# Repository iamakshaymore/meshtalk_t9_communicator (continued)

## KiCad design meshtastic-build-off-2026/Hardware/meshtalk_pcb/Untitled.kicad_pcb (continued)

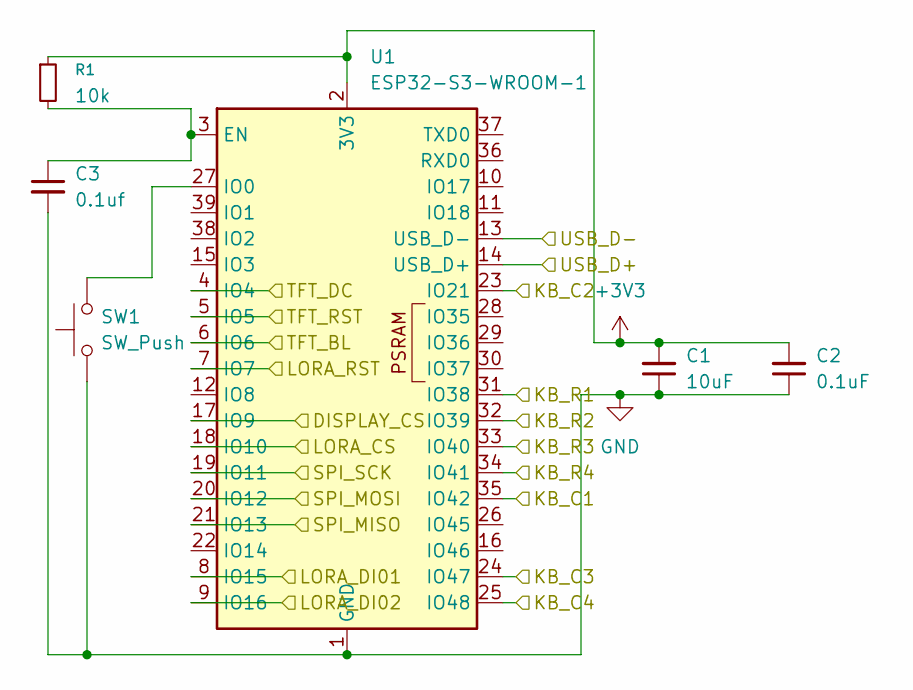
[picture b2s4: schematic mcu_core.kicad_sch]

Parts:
C1: 10uF; C_0805_2012Metric
C2: 0.1uF; C_0805_2012Metric
C3: 0.1uf; C_0805_2012Metric
R1: 10k; R_0805_2012Metric
SW1: SW_Push; SW_Push_1P1T_NO_CK_KSC6xxJ
U1: ESP32-S3-WROOM-1

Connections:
+3V3: C1.2, C2.2, R1.1, U1.2 (3V3); also elsewhere on the board
/LoRa_Radio/LORA_CS: U1.18 (IO10); also elsewhere on the board
/LoRa_Radio/LORA_DI01: U1.8 (IO15); also elsewhere on the board
/LoRa_Radio/LORA_DI02: U1.9 (IO16); also elsewhere on the board
/LoRa_Radio/LORA_RST: U1.7 (IO7); also elsewhere on the board
/LoRa_Radio/SPI_MISO: U1.21 (IO13); also elsewhere on the board
/LoRa_Radio/SPI_MOSI: U1.20 (IO12); also elsewhere on the board
/LoRa_Radio/SPI_SCK: U1.19 (IO11); also elsewhere on the board
/MCU_Core/DISPLAY_CS: U1.17 (IO9); also elsewhere on the board
/MCU_Core/KB_C1: U1.35 (IO42); also elsewhere on the board
/MCU_Core/KB_C2: U1.23 (IO21); also elsewhere on the board
/MCU_Core/KB_C3: U1.24 (IO47); also elsewhere on the board
/MCU_Core/KB_C4: U1.25 (IO48); also elsewhere on the board
/MCU_Core/KB_R1: U1.31 (IO38); also elsewhere on the board
/MCU_Core/KB_R2: U1.32 (IO39); also elsewhere on the board
/MCU_Core/KB_R3: U1.33 (IO40); also elsewhere on the board
/MCU_Core/KB_R4: U1.34 (IO41); also elsewhere on the board
/MCU_Core/TFT_BL: U1.6 (IO6); also elsewhere on the board
/MCU_Core/TFT_DC: U1.4 (IO4); also elsewhere on the board
/MCU_Core/TFT_RST: U1.5 (IO5); also elsewhere on the board
/MCU_Core/USB_D+: U1.14 (USB_D+); also elsewhere on the board
/MCU_Core/USB_D-: U1.13 (USB_D-); also elsewhere on the board
GND: C1.1, C2.1, C3.2, SW1.1, U1.1 (GND), U1.40 (GND), U1.41 (GND); also elsewhere on the board
unnamed: C3.1, R1.2, U1.3 (EN)
unnamed: SW1.2, U1.27 (IO0)

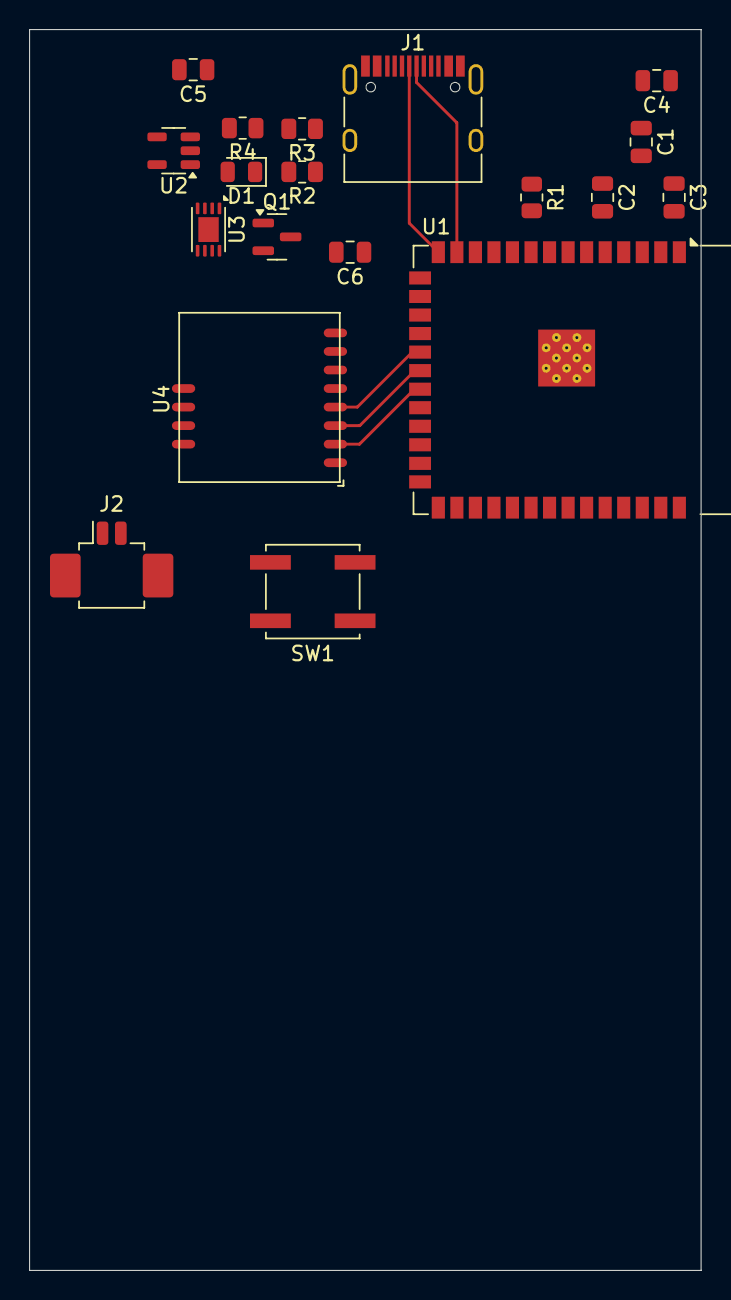
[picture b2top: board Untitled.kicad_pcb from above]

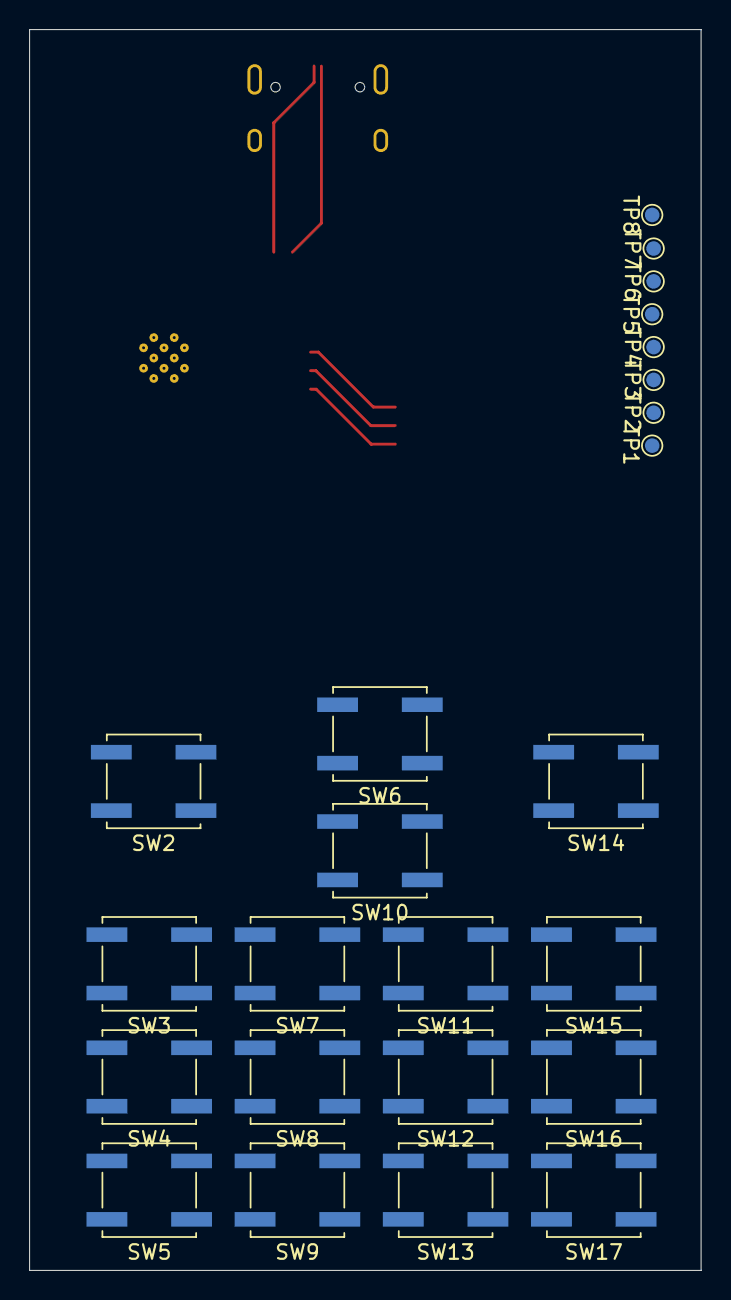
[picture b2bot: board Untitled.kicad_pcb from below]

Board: 4 copper layers, 46.0 x 85.0 mm, 43 parts (24 on the bottom side), 32 nets.

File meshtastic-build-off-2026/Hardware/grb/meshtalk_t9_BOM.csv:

"Reference","Qty","Value","DNP","Exclude from BOM","Exclude from Board","Footprint","Datasheet","Description"
"C1,C4,C5","3","10uF","","","","Capacitor_SMD:C_0805_2012Metric","~","Unpolarized capacitor, small symbol"
"C2,C6","2","0.1uF","","","","Capacitor_SMD:C_0805_2012Metric","~","Unpolarized capacitor, small symbol"
"C3","1","0.1uf","","","","Capacitor_SMD:C_0805_2012Metric","~","Unpolarized capacitor, small symbol"
"D1","1","D_Schottky","","","","LED_SMD:LED_0805_2012Metric","~","Schottky diode"
"J1","1","USB_C_Receptacle_USB2.0_16P","","","","Connector_USB:USB_C_Receptacle_HRO_TYPE-C-31-M-12","https://www.usb.org/sites/default/files/documents/usb_type-c.zip","USB 2.0-only 16P Type-C Receptacle connector"
"J2","1","Conn_01x02_Socket","","","","Connector_Molex:Molex_PicoBlade_53261-0271_1x02-1MP_P1.25mm_Horizontal","~","Generic connector, single row, 01x02, script generated"
"Q1","1","Q_PMOS_GSD","","","","Package_TO_SOT_SMD:SOT-23","~","P-MOSFET transistor, gate/source/drain"
"Q2","1","2N7002","","","","Package_TO_SOT_SMD:SOT-23","https://www.onsemi.com/pub/Collateral/NDS7002A-D.PDF","0.115A Id, 60V Vds, N-Channel MOSFET, SOT-23"
"R1","1","10k","","","","Resistor_SMD:R_0805_2012Metric","~","Resistor, small symbol"
"R2,R3","2","5.1k","","","","Resistor_SMD:R_0805_2012Metric","~","Resistor, small symbol"
"R4","1","100k","","","","Resistor_SMD:R_0805_2012Metric","~","Resistor, small symbol"
"R5","1","390k","","","","Capacitor_SMD:C_0805_2012Metric","~","Resistor, small symbol"
"R6","1","100k","","","","Capacitor_SMD:C_0805_2012Metric","~","Resistor, small symbol"
"R7","1","2k","","","","Capacitor_SMD:C_0805_2012Metric","~","Resistor, small symbol"
"SW1,SW2,SW3,SW4,SW5,SW6,SW7,SW8,SW9,SW10,SW11,SW12,SW13,SW14,SW15,SW16,SW17","17","SW_Push","","","","Button_Switch_SMD:SW_SPST_Omron_B3FS-100xP","~","Push button switch, generic, two pins"
"TP1,TP2,TP3,TP4,TP5,TP6,TP7,TP8","8","TestPoint","","","","TestPoint:TestPoint_Pad_D1.0mm","~","test point"
"U1","1","ESP32-S3-WROOM-1","","","","RF_Module:ESP32-S3-WROOM-1","https://www.espressif.com/sites/default/files/documentation/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","RF Module, ESP32-S3 SoC, Wi-Fi 802.11b/g/n, Bluetooth, BLE, 32-bit, 3.3V, onboard antenna, SMD"
"U2","1","AP2112K-3.3","","","","Package_TO_SOT_SMD:SOT-23-5","https://www.diodes.com/assets/Datasheets/AP2112.pdf","600mA low dropout linear regulator, with enable pin, 3.8V-6V input voltage range, 3.3V fixed positive output, SOT-23-5"
"U3","1","MCP73831-2-MC","","","","Package_DFN_QFN:DFN-8-1EP_3x2mm_P0.5mm_EP1.7x1.4mm","http://ww1.microchip.com/downloads/en/DeviceDoc/20001984g.pdf","Single cell, Li-Ion/Li-Po charge management controller, 4.20V, Tri-State Status Output, in DFN-8 package"
"U4","1","Wio-SX1262","","","","Module:Wio SX1262","",""

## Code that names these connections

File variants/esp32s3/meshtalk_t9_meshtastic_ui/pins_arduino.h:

#ifndef Pins_Arduino_h
#define Pins_Arduino_h

#include <stdint.h>

// Espressif's standard VID/PID for custom ESP32-S3 builds
#define USB_VID 0x303a
#define USB_PID 0x1001

// No I2C devices on MeshTalk T9 — dummy values to prevent Wire.begin()
// from conflicting with TFT_BL on GPIO4
static const uint8_t SDA =  3;
static const uint8_t SCL = 46;

// Default SPI maps to LoRa radio bus
static const uint8_t MISO = 11;  // SPI_MISO_LORA
static const uint8_t SCK  = 13;  // SPI_SCK_LORA
static const uint8_t MOSI = 12;  // SPI_MOSI_LORA
static const uint8_t SS   = 21;  // LORA_CS

#endif /* Pins_Arduino_h */

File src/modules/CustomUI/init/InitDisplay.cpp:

#include "InitDisplay.h"
#include <LovyanGFX.hpp>
#include <Arduino.h>

#ifdef ESP32
#include <esp_heap_caps.h>
#include <driver/gpio.h>  // For gpio_hold_en() function
#endif

// Add missing logging
#ifndef LOG_INFO
#define LOG_INFO(format, ...) Serial.printf("[INFO] " format "\n", ##__VA_ARGS__)
#endif

// Display pins - conditional for V3, V4, and MESHTALK_T9 variants
#if defined(VARIANT_heltec_v4_custom)
    // Heltec V4 Custom with external ST7789
    #define TFT_MOSI 5  // Data line - GPIO33 (DISP_MOSI)
    #define TFT_SCLK 45  // Clock line - GPIO47 (DISP_SCK)
    #define TFT_CS   6  // Chip select - GPIO48 (DISP_CS)
    #define TFT_DC   21  // Data/Command - GPIO21 (DISP_DC)
    #define TFT_RST  3  // Reset - GPIO17 (DISP_RST)
    #define TFT_BL   4  // Backlight - GPIO34 (DISP_BL)
#elif defined(MESHTALK_T9)
    // MeshTalk T9 with external ST7789 (SPI Bus 2)
    #define TFT_MOSI 16  // Data line (DIN) - GPIO16
    #define TFT_SCLK 15  // Clock line (CLK) - GPIO15
    #define TFT_CS   7   // Chip select - GPIO7
    #define TFT_DC   6   // Data/Command - GPIO6
    #define TFT_RST  5   // Reset - GPIO5
    #define TFT_BL   4   // Backlight - GPIO4
#else
    // Heltec V3 Custom with external ST7789 (default)
    #define TFT_MOSI 5   // Data line - GPIO5
    #define TFT_SCLK 7   // Clock line - GPIO7
    #define TFT_CS   6   // Chip select - GPIO6
    #define TFT_DC   2   // Data/Command - GPIO2
    #define TFT_RST  3   // Reset - GPIO3
    #define TFT_BL   4   // Backlight - GPIO4
#endif

/**
 * LovyanGFX optimized display class for ST7789 with ESP32-S3
 * Configured for maximum performance with automatic PSRAM and DMA
 */
class LGFX : public lgfx::LGFX_Device
{
    lgfx::Panel_ST7789 _panel_instance;
    lgfx::Bus_SPI _bus_instance;
    lgfx::Light_PWM _light_instance;    

  public:
    LGFX(void)
    {
        {
            auto cfg = _bus_instance.config();

            // Configure SPI3_HOST to avoid conflict with LoRa radio on SPI2_HOST
            cfg.spi_host = SPI3_HOST;  // Use SPI3 instead of SPI2 to avoid LoRa conflict
            cfg.spi_mode = 0;
            cfg.freq_write = 45000000; // 45MHz write speed
            cfg.freq_read = 16000000;  // 16MHz read speed
            cfg.spi_3wire = false;
            cfg.use_lock = true;               // Enable transaction locking
            cfg.dma_channel = SPI_DMA_CH_AUTO; // Auto DMA for better performance
            cfg.pin_sclk = TFT_SCLK;
            cfg.pin_mosi = TFT_MOSI;
            cfg.pin_miso = -1;               // MISO not connected
            cfg.pin_dc = TFT_DC;

            _bus_instance.config(cfg);
            _panel_instance.setBus(&_bus_instance);
        }

        {
            auto cfg = _panel_instance.config();

            cfg.pin_cs = TFT_CS;
            cfg.pin_rst = TFT_RST;
            cfg.pin_busy = -1;
            
            // Display configuration for 240x320 ST7789
            cfg.panel_width = 240;
            cfg.panel_height = 320;
            cfg.offset_x = 0;
            cfg.offset_y = 0;
            cfg.offset_rotation = 0;
            #if defined(MESHTALK_T9)
            cfg.offset_rotation = 2; // Rotate display 180 degrees for MESHTALK_T9
            #endif

            cfg.dummy_read_pixel = 8;
            cfg.dummy_read_bits = 1;
            cfg.readable = false;
            cfg.invert = true;  // Try inverting display colors
            cfg.rgb_order = false;
            cfg.dlen_16bit = false;

            _panel_instance.config(cfg);
        }

        {
            auto cfg = _light_instance.config();

            cfg.pin_bl = TFT_BL;
            cfg.invert = false;
            cfg.freq = 12000;
            cfg.pwm_channel = 7;

            _light_instance.config(cfg);
            _panel_instance.setLight(&_light_instance);
        }

        setPanel(&_panel_instance);
    }
};

InitDisplay::InitDisplay() : tft(nullptr), initialized(false) {
    LOG_INFO("🔧 InitDisplay: Constructor");
}

InitDisplay::~InitDisplay() {
    cleanup();
}

bool InitDisplay::init() {
    LOG_INFO("🔧 InitDisplay: Initializing ST7789 display with LovyanGFX...");
    #if defined(VARIANT_heltec_v4_custom)
    // Initialize Vext (external power) first - V4 uses GPIO36 active low
        pinMode(36, OUTPUT);
        digitalWrite(36, LOW); // Turn ON external power (active low)
        delay(200); // Wait for power to stabilize
        LOG_INFO("🔧 InitDisplay: External power (Vext) enabled on GPIO36");
    #endif
    
    // Initialize backlight pin first
    if (TFT_BL >= 0) {
        pinMode(TFT_BL, OUTPUT);
        digitalWrite(TFT_BL, HIGH); // Turn on backlight
        delay(100);
        LOG_INFO("🔧 InitDisplay: Backlight enabled on GPIO %d", TFT_BL);
    }
    
    // Create the LovyanGFX display instance
    tft = new LGFX();
    
    // Initialize the display - LovyanGFX handles SPI setup automatically
    tft->init();
    
    // Report memory status and PSRAM availability
    LOG_INFO("🔧 InitDisplay: Memory Status Report:");
    LOG_INFO("🔧 InitDisplay: - Total Heap: %u bytes (%.1fKB)", (unsigned int)ESP.getHeapSize(), ESP.getHeapSize()/1024.0);
    LOG_INFO("🔧 InitDisplay: - Free Heap: %u bytes (%.1fKB)", (unsigned int)ESP.getFreeHeap(), ESP.getFreeHeap()/1024.0);
    
#if defined(CONFIG_SPIRAM_SUPPORT) && defined(BOARD_HAS_PSRAM)
    size_t psramSize = ESP.getPsramSize();
    if (psramSize > 0) {
        size_t freePsram = heap_caps_get_free_size(MALLOC_CAP_SPIRAM);
        LOG_INFO("🔧 InitDisplay: - PSRAM Total: %u bytes (%.1fMB)", (unsigned int)psramSize, psramSize/(1024.0*1024.0));
        LOG_INFO("🔧 InitDisplay: - PSRAM Free: %u bytes (%.1fMB)", (unsigned int)freePsram, freePsram/(1024.0*1024.0));
        LOG_INFO("🔧 InitDisplay: ✅ PSRAM ENABLED for graphics operations");
        tft->setColorDepth(16); // Use 16-bit color to optimize PSRAM usage
    } else {
        LOG_INFO("🔧 InitDisplay: ⚠️  No PSRAM detected, using standard configuration");
    }
#else
    LOG_INFO("🔧 InitDisplay: ⚠️  PSRAM support not compiled in");
#endif
    
    delay(100);
    tft->setRotation(1); // Landscape mode: 320x240
    tft->fillScreen(0x0000); // Pure black background for power efficiency
    
    // Add debug logging for pin configuration
    LOG_INFO("🔧 InitDisplay: Pin Configuration - MOSI:%d SCK:%d CS:%d DC:%d RST:%d BL:%d", 
             TFT_MOSI, TFT_SCLK, TFT_CS, TFT_DC, TFT_RST, TFT_BL);
    
    // Test display with a simple pattern
    tft->fillScreen(0x001F); // Blue background
    delay(500);
    tft->fillScreen(0x0000); // Black background
    
    initialized = true;
    LOG_INFO("🔧 InitDisplay: LovyanGFX initialized with 80MHz SPI, DMA, and PSRAM support");
    return true;
}

void InitDisplay::cleanup() {

    if (tft) {
        LOG_INFO("🔧 InitDisplay: Starting enhanced display shutdown sequence");
        
        // Phase 1: Proper ST7789 Controller Shutdown
        // Send sleep command to enter low power mode first
        tft->sleep();
        tft->setBrightness(0);
        
        // Send the ST7789 deep sleep command (0x10) directly for complete charge pump shutdown
        tft->writecommand(0x10); 
        delay(120); // Mandatory delay for charge pump decay
        
        // Phase 2: Latch Backlight OFF with Hold
        // We explicitly drive the pin LOW (assuming active High logic).
        pinMode(TFT_BL, OUTPUT);
        digitalWrite(TFT_BL, LOW);
        
        // CRITICAL: Enable RTC Pad Hold
        // This freezes the pin state at the I/O MUX level during deep sleep.
        gpio_hold_en((gpio_num_t)TFT_BL);
        
        // Phase 3: Isolate Data Lines (Prevent Parasitic Power)
        // When VCC is cut, logic High signals can feed power through ESD diodes.
        // We drive critical lines LOW.
        pinMode(TFT_CS, OUTPUT);
        digitalWrite(TFT_CS, LOW); // Drive CS low to isolate SPI
        gpio_hold_en((gpio_num_t)TFT_CS);
        
        // Also isolate other critical SPI lines if needed
        pinMode(TFT_DC, OUTPUT);
        digitalWrite(TFT_DC, LOW);
        gpio_hold_en((gpio_num_t)TFT_DC);
        
        // Phase 4: Cut External Power (Vext)
        // Heltec V3 Vext Logic: High = OFF (Active Low Enable) 
        // GPIO 36 controls external 3.3V rail
        pinMode(36, OUTPUT); // Vext pin (GPIO 36)
        digitalWrite(36, HIGH); // Turn OFF external power (active low)
        gpio_hold_en((gpio_num_t)36);
        
        delete tft;
        tft = nullptr;
        
        LOG_INFO("🔧 InitDisplay: Enhanced shutdown complete - All power paths disabled with hold");
    }
    
    initialized = false;
}

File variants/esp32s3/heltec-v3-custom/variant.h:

/*
 * CustomUIModule - A T9 Matrix Keypad & Display Driver for Meshtastic
 * Copyright (C) 2026 Akshay Pramod More
 *
 * This program is free software: you can redistribute it and/or modify
 * it under the terms of the GNU General Public License as published by
 * the Free Software Foundation, either version 3 of the License, or
 * (at your option) any later version.
 *
 * This program is distributed in the hope that it will be useful,
 * but WITHOUT ANY WARRANTY; without even the implied warranty of
 * MERCHANTABILITY or FITNESS FOR A PARTICULAR PURPOSE.  See the
 * GNU General Public License for more details.
 */

#define LED_PIN LED

// Completely disable built-in OLED since we're using custom TFT
// Comment out USE_SSD1306 to disable built-in display initialization
// #define USE_SSD1306 // Disabled - using external ST7789 TFT instead

// Keep the original I2C pins available but don't use for display
#define I2C_SDA SDA_OLED 
#define I2C_SCL SCL_OLED

// Enable secondary bus for external peripherals
#define I2C_SDA1 SDA
#define I2C_SCL1 SCL

#define VEXT_ENABLE Vext // active low, powers the oled display and the lora antenna boost
#define BUTTON_PIN 0

#define ADC_CTRL 37
#define ADC_CTRL_ENABLED LOW
#define BATTERY_PIN 1 // A battery voltage measurement pin, voltage divider connected here to measure battery voltage
#define ADC_CHANNEL ADC_CHANNEL_0
#define ADC_ATTENUATION ADC_ATTEN_DB_2_5 // lower dB for high resistance voltage divider
#define ADC_MULTIPLIER 4.9 * 1.045

#define USE_SX1262

#define LORA_DIO0 -1 // a No connect on the SX1262 module
#define LORA_RESET 12
#define LORA_DIO1 14 // SX1262 IRQ
#define LORA_DIO2 13 // SX1262 BUSY
#define LORA_DIO3    // Not connected on PCB, but internally on the TTGO SX1262, if DIO3 is high the TXCO is enabled

#define LORA_SCK 9
#define LORA_MISO 11
#define LORA_MOSI 10
#define LORA_CS 8

#define SX126X_CS LORA_CS
#define SX126X_DIO1 LORA_DIO1
#define SX126X_BUSY LORA_DIO2
#define SX126X_RESET LORA_RESET

#define SX126X_DIO2_AS_RF_SWITCH
#define SX126X_DIO3_TCXO_VOLTAGE 1.8

#define HAS_32768HZ 1

// Define our variant name for conditional compilation
#define VARIANT_heltec_v3_custom 1
#define HELTEC_V3_CUSTOM 1

// Force disable any screen-related modules that might interfere
#define HAS_SCREEN 0

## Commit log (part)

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2026-01-12 support for v4 custom variant
2026-01-12 for sync
2026-01-26 V4 updates
2026-01-26 UI enhancements, stack screen arch
2026-01-26 Copyrights
2026-06-03 Push Latest Code
2026-06-03 Compatibility with last merge
2026-06-03 MESHTASTIC Build-Off 2026
2026-06-04 Update folder
2026-06-08 hardware
2026-06-08 Working DRC
2026-06-08 For Review
2026-06-09 updated PCB
2026-06-09 deletion
2026-06-09 update power rails and vias width
2026-06-09 images
2026-06-09 rename + battery % + boot btn changed to reset + fix battery chrging
2026-06-10 grb files
2026-06-19 Replace AP2112K-3.3 with AP7361C-33E Connected LORA RF_SW1 to GPIO Added ESD Added mounting holes for display (Waveshare 2 inch) Added Boot and Reset buttons made power rails thicker added dedicated 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
2026-06-19 update board images
2026-06-19 Images in readme
2026-06-24 PCB Updates - Align net names Clearence for esp32 antenna
